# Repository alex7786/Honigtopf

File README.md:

# Honigtopf

Arduino programm to control a honey-kettle

Used libraries:  
http://www.pjrc.com/teensy/arduino_libraries/OneWire.zip  
https://github.com/milesburton/Arduino-Temperature-Control-Library  
https://www.arduino.cc/en/Reference/LiquidCrystal

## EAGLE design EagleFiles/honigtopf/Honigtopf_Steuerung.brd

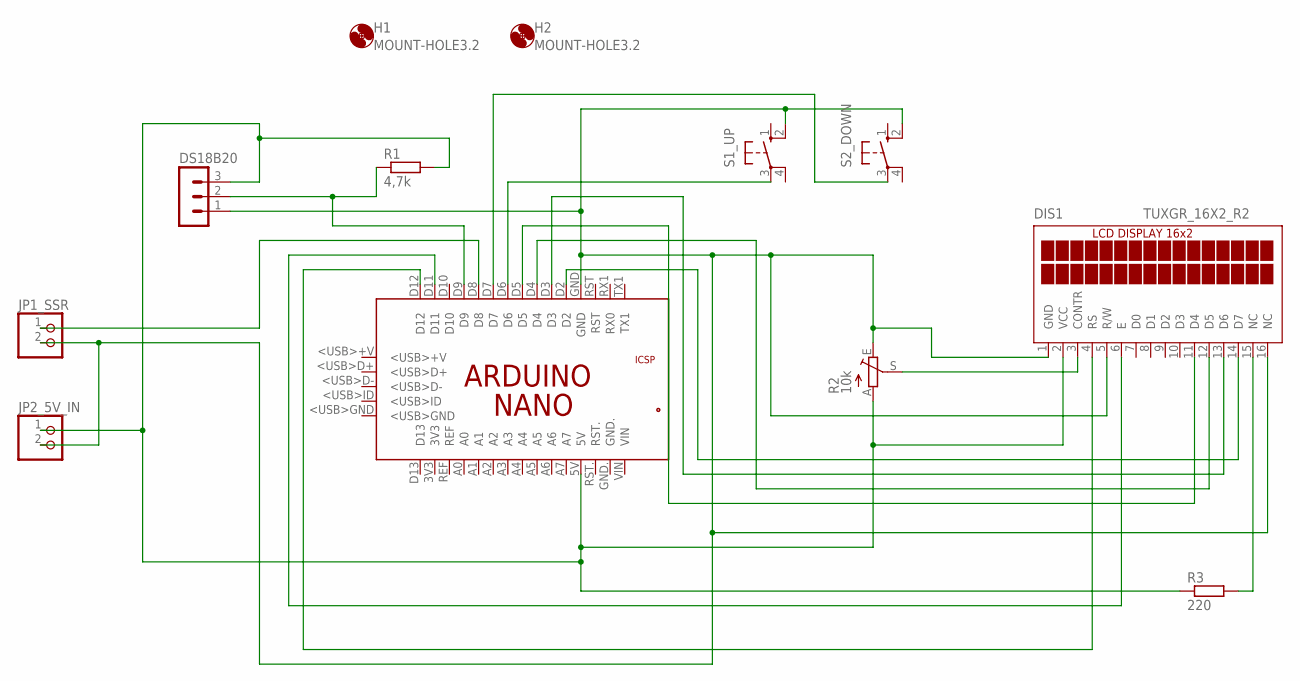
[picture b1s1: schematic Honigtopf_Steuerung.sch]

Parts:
DIS1: TUXGR_16X2_R2
DS18B20: MA03-1
H1, H2: MOUNT-HOLE3.2; 3,2
JP1_SSR, JP2_5V_IN: PINHD-1X2; 1X02
PCB1: ARDUINO_NANO
R1: 4,7k; 0411/15
R2: 10k; CA14V
R3: 220; 0411/15
S1_UP, S2_DOWN: 10-XX; B3F-10XX

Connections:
5V: DIS1.2 (VCC), DS18B20.3, JP2_5V_IN.1, PCB1.5V, R1.2, R2.A, R3.1
GND: DIS1.1 (GND), DIS1.5 (R/W), DIS1.16 (NC), DS18B20.1, JP1_SSR.2, JP2_5V_IN.2, PCB1.GND, R2.E, S1_UP.2 (S1), S2_DOWN.2 (S1)
unnamed: DS18B20.2, PCB1.D9, R1.1
unnamed: DIS1.15 (NC), R3.2
unnamed: JP1_SSR.1, PCB1.D8
unnamed: PCB1.D6, S1_UP.3
unnamed: PCB1.D7, S2_DOWN.3
unnamed: DIS1.3 (CONTR), R2.S
unnamed: DIS1.4 (RS), PCB1.D12
unnamed: DIS1.6 (E), PCB1.D11
unnamed: DIS1.11 (D4), PCB1.D5
unnamed: DIS1.12 (D5), PCB1.D4
unnamed: DIS1.13 (D6), PCB1.D3
unnamed: DIS1.14 (D7), PCB1.D2

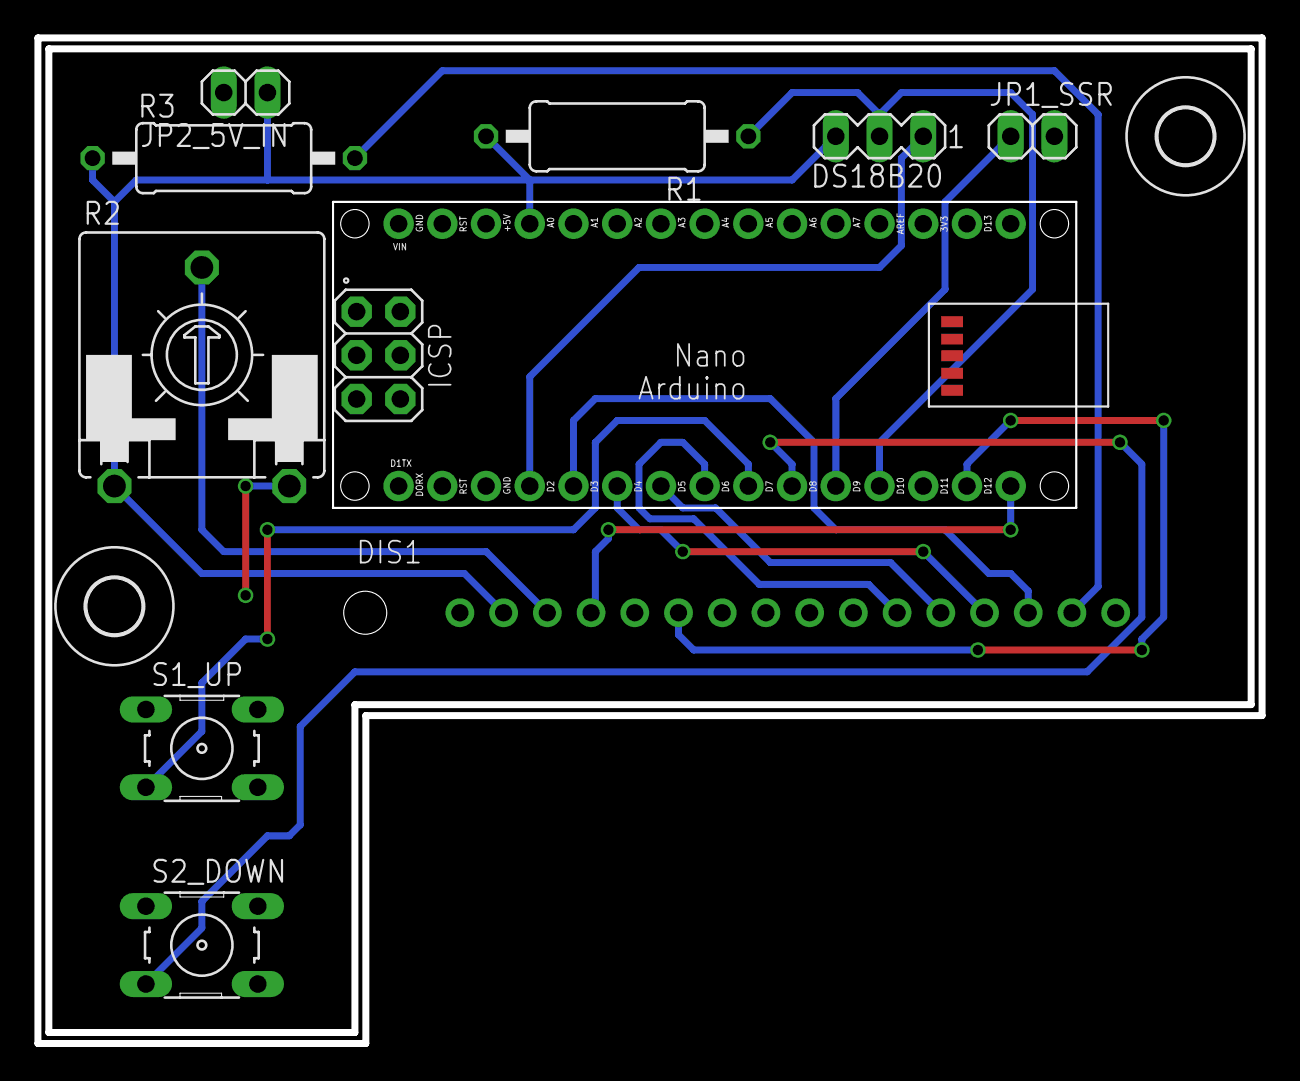
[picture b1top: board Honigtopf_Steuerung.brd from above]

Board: 2 copper layers, 71.1 x 58.4 mm, 12 parts (0 on the bottom side), 14 nets.

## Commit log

2017-04-07 Initial Upload
2017-04-07 Added Libraries
2017-04-07 Added readTemp
2017-04-07 added comment
2017-04-07 changed comments
2017-04-07 Added comments and tempControl method
2017-04-07 added Eagle files
2017-04-07 added eagle schematic
2017-04-17 corrected currentTemp var and added min and max Temp
2017-05-05 changed pins to const
2017-05-05 added supply pins
2017-05-05 added ngc files
2017-05-05 added gerber files
2017-05-30 changed standard temp to 39
